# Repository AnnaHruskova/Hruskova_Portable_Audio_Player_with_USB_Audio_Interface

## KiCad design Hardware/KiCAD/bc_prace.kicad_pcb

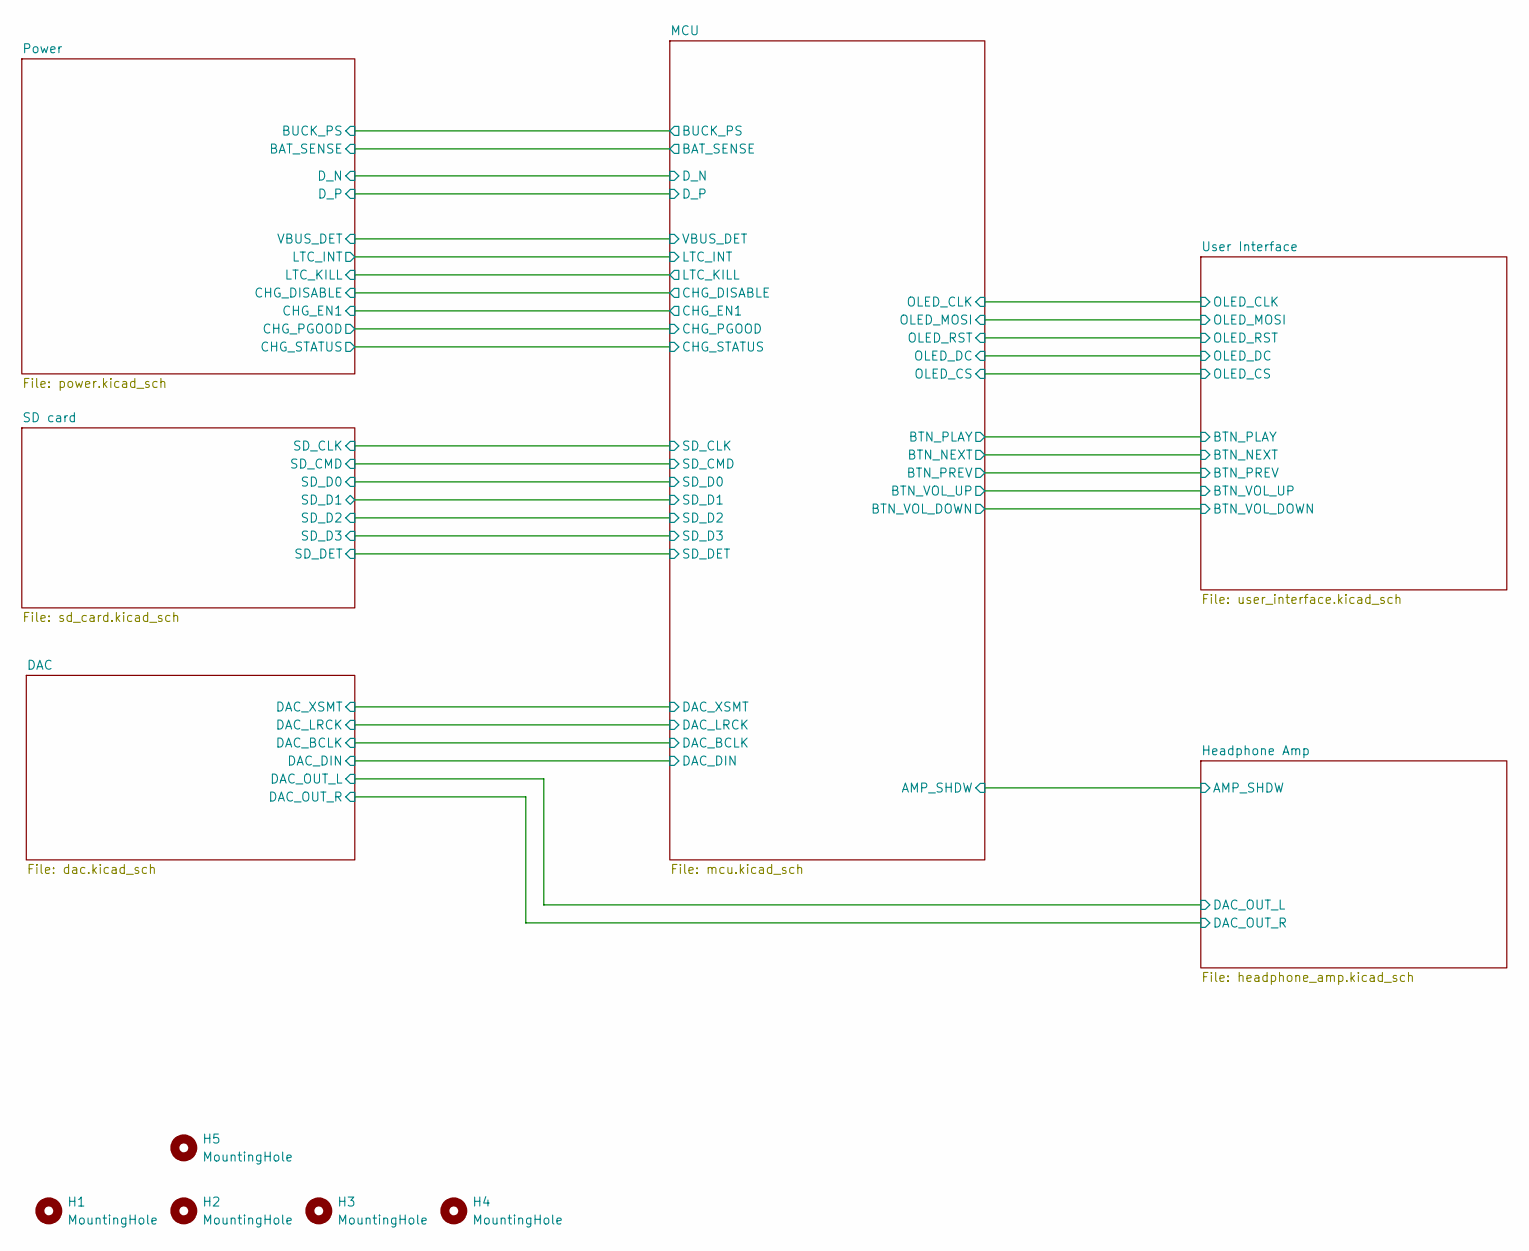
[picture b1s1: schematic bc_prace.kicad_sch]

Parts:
H1, H2, H3, H4: MountingHole; MountingHole_3.2mm_M3
H5: MountingHole; MountingHole_2.7mm

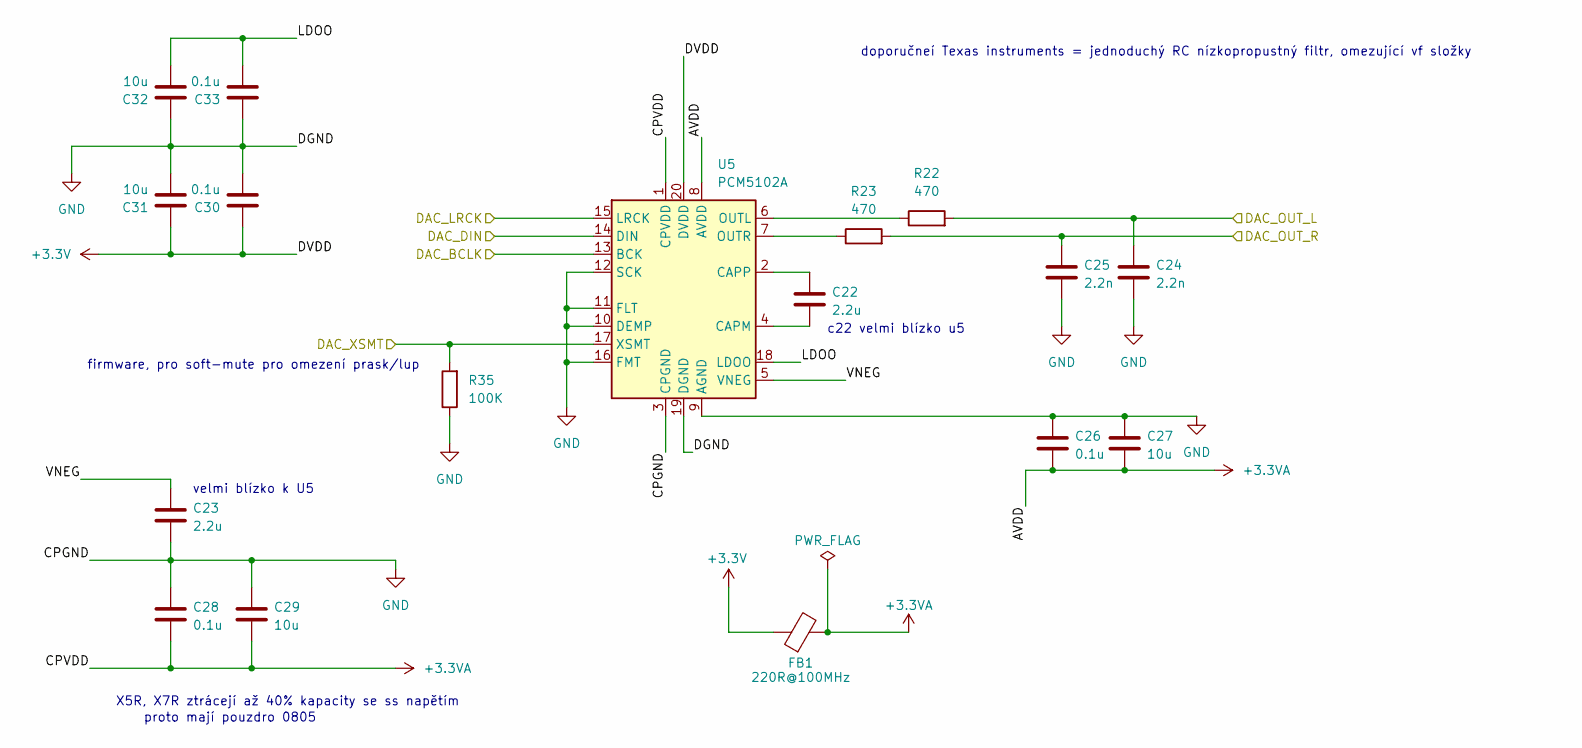
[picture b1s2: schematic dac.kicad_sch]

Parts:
C22, C23: 2.2u; C_0805_2012Metric; MPN CL21B225KOFNNNE
C24, C25: 2.2n; C_0603_1608Metric; MPN CC0603JRNPO9BN222
C26, C28, C33: 0.1u; C_0603_1608Metric; MPN CC0603KRX7R9BB104
C27, C29, C31: 10u; C_0805_2012Metric; MPN CL21A106KAYNNNE
C30: 0.1u; C_0805_2012Metric; MPN CC0805KRX7R9BB104
C32: 10u; C_0603_1608Metric; MPN CL10A106KP8NNNC
FB1: 220R@100MHz; L_0805_2012Metric; MPN BLM21PG221SN1D
R22, R23: 470; R_0603_1608Metric; MPN RC0603FR-07470RL
R35: 100K; R_0603_1608Metric; MPN RC0603FR-07100KL
U5: PCM5102A; TSSOP-20_4.4x6.5mm_P0.65mm; MPN PCM5102APWR

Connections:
+3.3V: C30.2, C31.2, FB1.1, U5.20 (DVDD); also elsewhere on the board
+3.3VA: C26.1, C27.1, C28.1, C29.1, FB1.2, U5.1 (CPVDD), U5.8 (AVDD)
/DAC/DAC_BCLK: U5.13 (BCK); also elsewhere on the board
/DAC/DAC_DIN: U5.14 (DIN); also elsewhere on the board
/DAC/DAC_LRCK: U5.15 (LRCK); also elsewhere on the board
/DAC/DAC_OUT_L: C24.2, R22.2; also elsewhere on the board
/DAC/DAC_OUT_R: C25.2, R23.2; also elsewhere on the board
/DAC/DAC_XSMT: R35.2, U5.17 (XSMT); also elsewhere on the board
/DAC/LDOO: C32.1, C33.1, U5.18 (LDOO)
/DAC/VNEG: C23.2, U5.5 (VNEG)
GND: C23.1, C24.1, C25.1, C26.2, C27.2, C28.2, C29.2, C30.1, C31.1, C32.2, C33.2, R35.1, U5.3 (CPGND), U5.9 (AGND), U5.10 (DEMP), U5.11 (FLT), U5.12 (SCK), U5.16 (FMT), U5.19 (DGND); also elsewhere on the board
unnamed: C22.1, U5.4 (CAPM)
unnamed: C22.2, U5.2 (CAPP)
unnamed: R22.1, U5.6 (OUTL)
unnamed: R23.1, U5.7 (OUTR)

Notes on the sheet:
proto mají pouzdro 0805
velmi blízko k U5
doporučneí Texas instruments = jednoduchý RC nízkopropustný filtr, omezující vf složky
c22 velmi blízko u5
X5R, X7R ztrácejí až 40% kapacity se ss napětím
firmware, pro soft-mute pro omezení prask/lup

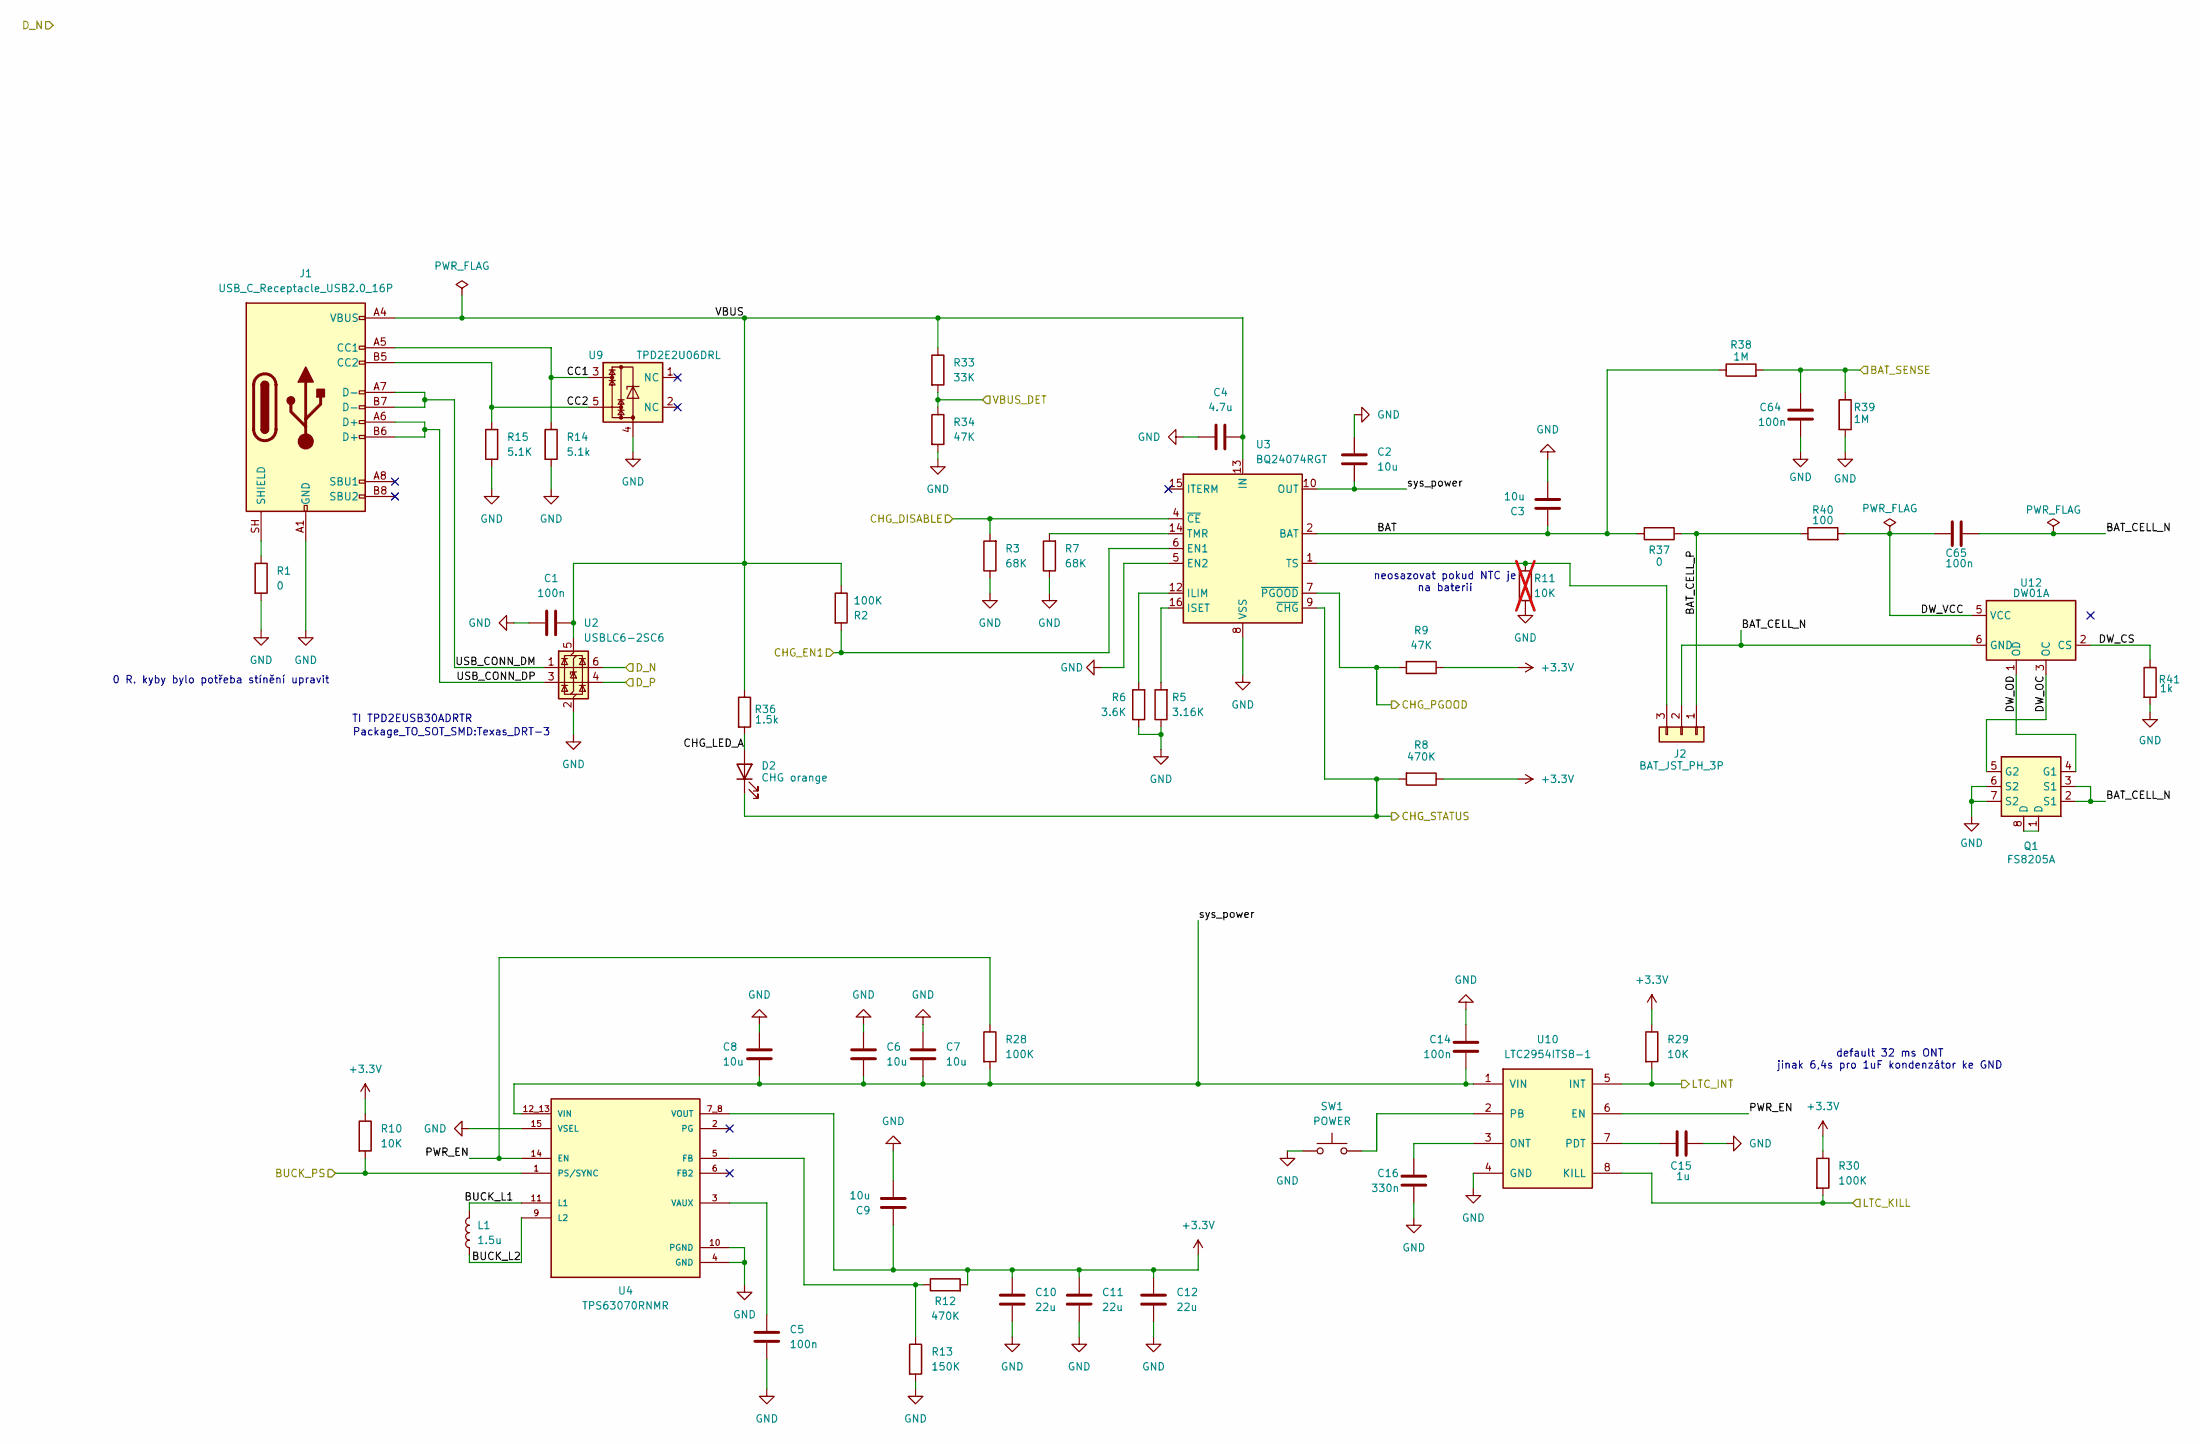
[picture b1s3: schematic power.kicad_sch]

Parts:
C1, C5, C14: 100n; C_0603_1608Metric; MPN CC0603KRX7R9BB104
C2: 10u; C_0805_2012Metric; MPN CL21B475KOFNNWE
C3, C6, C7, C8, C9: 10u; C_0805_2012Metric; MPN CL21A106KAYNNNE
C4: 4.7u; C_0603_1608Metric; MPN CL10A475KO8NNNC
C10, C11, C12: 22u; C_0805_2012Metric; MPN CL21A226MAQNNNE
C15: 1u; C_0603_1608Metric; MPN CL10A105KB8NNNC
C16: 330n; C_0603_1608Metric; MPN CC0603KRX7R7BB334
C64, C65: 100n; C_0805_2012Metric; MPN CC0805KRX7R9BB104
D2: CHG orange; LED_0805_2012Metric; MPN LED 0805 oranžová (doplnit)
J1: USB_C_Receptacle_USB2.0_16P; USB_C_Receptacle_GCT_USB4105-xx-A_16P_TopMnt_Horizontal; MPN USB4105-GF-A
J2: BAT_JST_PH_3P; JST_PH_B3B-PH-K_1x03_P2.00mm_Vertical; MPN B3B-PH-K-S(LF)(SN)
L1: 1.5u; L_Coilcraft_XxL4020; MPN XFL4020-152MEC
Q1: FS8205A; TSSOP-8_4.4x3mm_P0.65mm; MPN FS8205A
R1: 0; R_0603_1608Metric; MPN RC0603JR-070RL
R2, R28, R30: 100K; R_0603_1608Metric; MPN RC0603FR-07100KL
R3, R7: 68K; R_0603_1608Metric; MPN RC0603FR-0768KL
R5: 3.16K; R_0603_1608Metric
R6: 3.6K; R_0603_1608Metric; MPN RC0603FR-073K6L
R8, R12: 470K; R_0603_1608Metric; MPN RC0603FR-07470KL
R9, R34: 47K; R_0603_1608Metric; MPN RC0603FR-0747KL
R10, R29: 10K; R_0603_1608Metric; MPN RC0603FR-0710KL
R11: 10K; R_0603_1608Metric; MPN RC0603FR-0710KL; not fitted
R13: 150K; R_0603_1608Metric; MPN RC0603FR-07150KL
R14: 5.1k; R_0603_1608Metric; MPN RC0603FR-075K1L
R15: 5.1K; R_0603_1608Metric; MPN RC0603FR-075K1L
R33: 33K; R_0603_1608Metric; MPN RC0603FR-0733KL
R36: 1.5k; R_0805_2012Metric; MPN RC0805FR-071K5L
R37: 0; R_1206_3216Metric; MPN RC1206JR-070RL
R38, R39: 1M; R_0805_2012Metric; MPN RC0805FR-071ML
R40: 100; R_0805_2012Metric; MPN RC0805FR-07100RL
R41: 1k; R_0805_2012Metric; MPN RC0805FR-071KL
SW1: POWER; SW_Push_1P1T-MP_NO_Horizontal_Alps_SKRTLAE010; MPN SKRTLAE010
U2: USBLC6-2SC6; SOT-23-6; MPN USBLC6-2SC6
U3: BQ24074RGT; VQFN-16-1EP_3x3mm_P0.5mm_EP1.6x1.6mm
U4: TPS63070RNMR; VREG_TPS63070RNMR
U9: TPD2E2U06DRL; SOT-553; MPN TPD2E2U06DRLR
U10: LTC2954ITS8-1; TSOT-23-8; MPN LTC2954ITS8-1#TRMPBF
U12: DW01A; SOT-23-6; MPN DW01A

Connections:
+3.3V: C9.2, C10.2, C11.2, C12.2, R8.1, R9.1, R10.1, R12.2, R29.1, R30.1, U4.7_8 (VOUT); also elsewhere on the board
/MCU/BAT_SENSE: C64.1, R38.2, R39.1; also elsewhere on the board
/MCU/BUCK_PS: R10.2, U4.1 (PS/SYNC); also elsewhere on the board
/MCU/CHG_DISABLE: R3.2, U3.4 (~CE); also elsewhere on the board
/MCU/CHG_EN1: R2.2, U3.6 (EN1); also elsewhere on the board
/MCU/CHG_PGOOD: R9.2, U3.7 (~PGOOD); also elsewhere on the board
/MCU/CHG_STATUS: D2.1 (K), R8.2, U3.9 (~CHG); also elsewhere on the board
/MCU/D_N: U2.6 (I/O1); also elsewhere on the board
/MCU/D_P: U2.4 (I/O2); also elsewhere on the board
/MCU/LTC_INT: R29.2, U10.5 (INT); also elsewhere on the board
/MCU/LTC_KILL: R30.2, U10.8 (KILL); also elsewhere on the board
/MCU/VBUS_DET: R33.2, R34.1; also elsewhere on the board
/Power/BAT: C3.2, R37.2, R38.1, U3.2 (BAT), U3.3 (BAT)
/Power/BAT_CELL_N: C65.2, J2.2, Q1.2 (S1), Q1.3 (S1), U12.6 (GND)
/Power/BAT_CELL_P: J2.1, R37.1, R40.1
/Power/BUCK_L1: L1.2, U4.11 (L1)
/Power/BUCK_L2: L1.1, U4.9 (L2)
/Power/CC1: J1.A5 (CC1), R14.1, U9.3
/Power/CC2: J1.B5 (CC2), R15.2, U9.5
/Power/CHG_LED_A: D2.2 (A), R36.2
/Power/DW_CS: R41.1, U12.2 (CS)
/Power/DW_OC: Q1.5 (G2), U12.3 (OC)
/Power/DW_OD: Q1.4 (G1), U12.1 (OD)
/Power/DW_VCC: C65.1, R40.2, U12.5 (VCC)
/Power/PWR_EN: R28.1, U4.14 (EN), U10.6 (EN)
/Power/USB_CONN_DM: J1.A7 (D-), J1.B7 (D-), U2.1 (I/O1)
/Power/USB_CONN_DP: J1.A6 (D+), J1.B6 (D+), U2.3 (I/O2)
/Power/VBUS: C1.2, C4.2, J1.A4 (VBUS), J1.A9 (VBUS), J1.B4 (VBUS), J1.B9 (VBUS), R2.1, R33.1, R36.1, U2.5 (VBUS), U3.13 (IN)
/Power/sys_power: C2.2, C6.2, C7.2, C8.2, C14.2, R28.2, U3.10 (OUT), U3.11 (OUT), U4.12_13 (VIN), U10.1 (VIN)
GND: C1.1, C2.1, C3.1, C4.1, C5.2, C6.1, C7.1, C8.1, C9.1, C10.1, C11.1, C12.1, C14.1, C15.2, C16.2, C64.2, J1.A1 (GND), J1.A12 (GND), J1.B1 (GND), J1.B12 (GND), Q1.6 (S2), Q1.7 (S2), R1.2, R3.1, R5.1, R6.1, R7.1, R11.2, R13.2, R14.2, R15.1, R34.2, R39.2, R41.2, SW1.1, U2.2 (GND), U3.5 (EN2), U3.8 (VSS), U3.17 (VSS), U4.4 (GND), U4.10 (PGND), U4.15 (VSEL), U9.4, U10.4 (GND); also elsewhere on the board
unnamed: J1.SH (SHIELD), R1.1
unnamed: J2.3, R11.1, U3.1 (TS)
unnamed: Q1.1 (D), Q1.8 (D)
unnamed: R6.2, U3.12 (ILIM)
unnamed: R5.2, U3.16 (ISET)
unnamed: R7.2, U3.14 (TMR)
unnamed: R12.1, R13.1, U4.5 (FB)
unnamed: C5.1, U4.3 (VAUX)
unnamed: C16.1, U10.3 (ONT)
unnamed: SW1.2, U10.2 (PB)
unnamed: C15.1, U10.7 (PDT)

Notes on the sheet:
Package_TO_SOT_SMD:Texas_DRT-3
neosazovat pokud NTC je na baterii
default 32 ms ONT jinak 6,4s pro 1uF kondenzátor ke GND
0 R. kyby bylo potřeba stínění upravit
TI TPD2EUSB30ADRTR

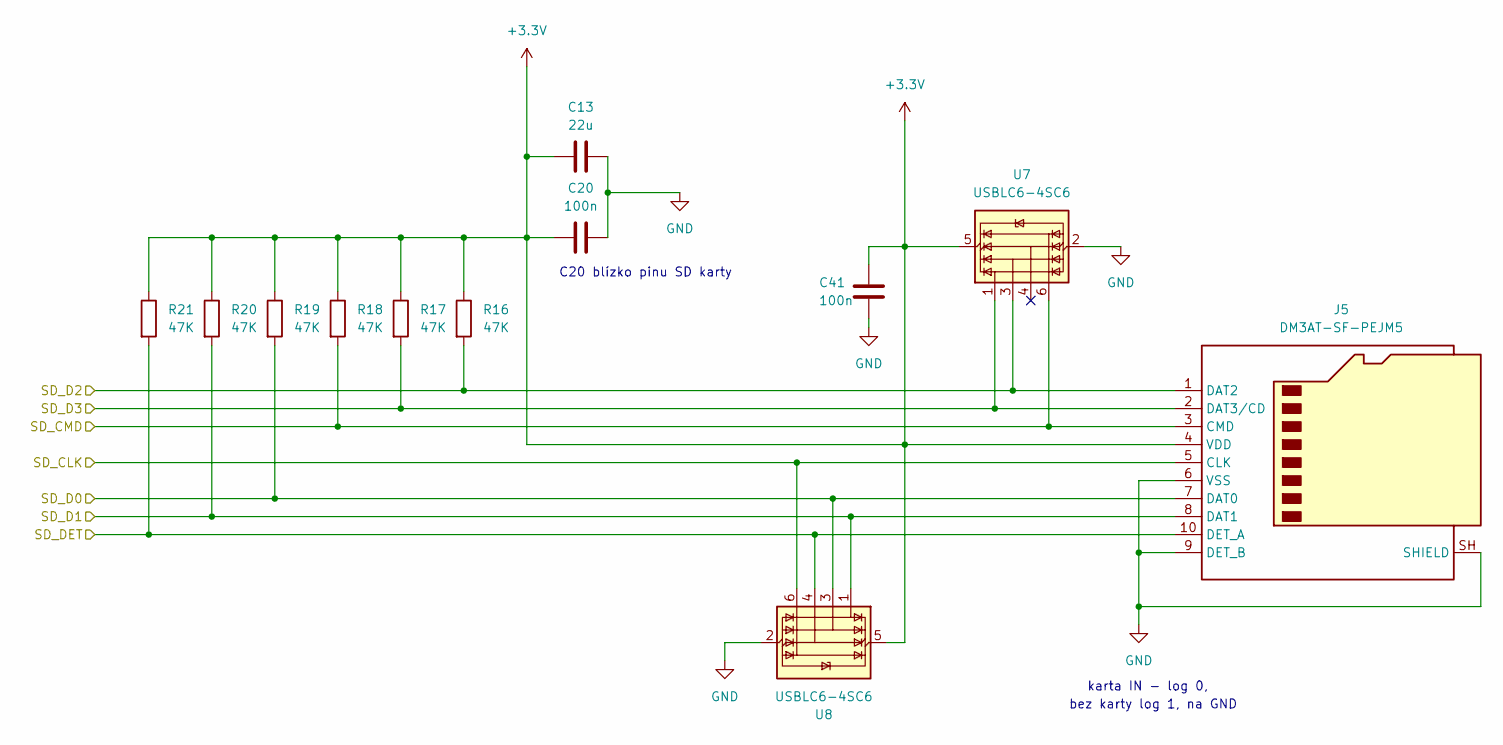
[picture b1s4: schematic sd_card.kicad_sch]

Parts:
C13: 22u; C_0805_2012Metric; MPN CL21A226MAQNNNE
C20, C41: 100n; C_0603_1608Metric; MPN CC0603KRX7R9BB104
J5: DM3AT-SF-PEJM5; microSD_HC_Hirose_DM3AT-SF-PEJM5; MPN DM3AT-SF-PEJM5
R16, R17, R18, R19, R20, R21: 47K; R_0603_1608Metric; MPN RC0603FR-0747KL
U7, U8: USBLC6-4SC6; SOT-23-6; MPN USBLC6-4SC6

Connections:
+3.3V: C13.2, C20.2, C41.1, J5.4 (VDD), R16.1, R17.1, R18.1, R19.1, R20.1, R21.1, U7.5 (VBUS), U8.5 (VBUS); also elsewhere on the board
/MCU/SD_CLK: J5.5 (CLK), U8.6 (I/O4); also elsewhere on the board
/MCU/SD_CMD: J5.3 (CMD), R18.2, U7.6 (I/O4); also elsewhere on the board
/MCU/SD_D0: J5.7 (DAT0), R19.2, U8.3 (I/O2); also elsewhere on the board
/MCU/SD_D1: J5.8 (DAT1), R20.2, U8.1 (I/O1); also elsewhere on the board
/MCU/SD_D2: J5.1 (DAT2), R16.2, U7.3 (I/O2); also elsewhere on the board
/MCU/SD_D3: J5.2 (DAT3/CD), R17.2, U7.1 (I/O1); also elsewhere on the board
/MCU/SD_DET: J5.10 (DET_A), R21.2, U8.4 (I/O3); also elsewhere on the board
GND: C13.1, C20.1, C41.2, J5.6 (VSS), J5.9 (DET_B), J5.SH (SHIELD), U7.2 (GND), U8.2 (GND); also elsewhere on the board

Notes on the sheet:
karta IN - log 0,
C20 blízko pinu SD karty
bez karty log 1, na GND

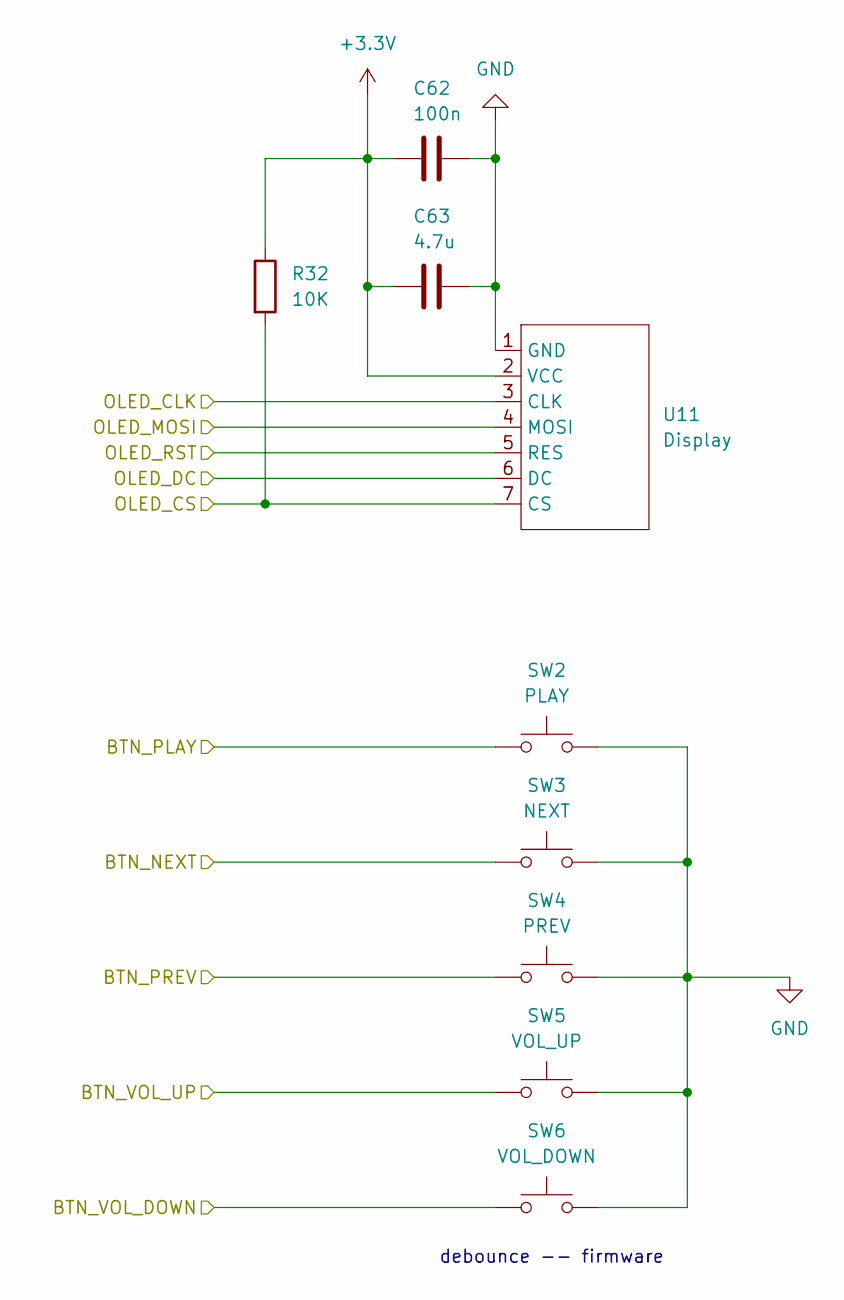
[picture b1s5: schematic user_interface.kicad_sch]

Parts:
C62: 100n; C_0603_1608Metric; MPN CC0603KRX7R9BB104
C63: 4.7u; C_0603_1608Metric; MPN CL10A475KO8NNNC
R32: 10K; R_0603_1608Metric; MPN RC0603FR-0710KL
SW2: PLAY; SW_SPST_PTS647_Sx70; MPN B3F-1000
SW3: NEXT; SW_SPST_PTS647_Sx70; MPN B3F-1000
SW4: PREV; SW_SPST_PTS647_Sx70; MPN B3F-1000
SW5: VOL_UP; SW_Push_1P1T-MP_NO_Horizontal_Alps_SKRTLAE010; MPN SKRTLAE010
SW6: VOL_DOWN; SW_Push_1P1T-MP_NO_Horizontal_Alps_SKRTLAE010; MPN SKRTLAE010
U11: Display; OLED_SPI_7pin_P2.54mm; MPN OLED modul SPI 7pin (zakoupený vlastní)

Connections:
+3.3V: C62.1, C63.1, R32.1, U11.2 (VCC); also elsewhere on the board
/MCU/BTN_NEXT: SW3.1; also elsewhere on the board
/MCU/BTN_PLAY: SW2.1; also elsewhere on the board
/MCU/BTN_PREV: SW4.1; also elsewhere on the board
/MCU/BTN_VOL_DOWN: SW6.1; also elsewhere on the board
/MCU/BTN_VOL_UP: SW5.1; also elsewhere on the board
/MCU/OLED_CLK: U11.3 (CLK); also elsewhere on the board
/MCU/OLED_CS: R32.2, U11.7 (CS); also elsewhere on the board
/MCU/OLED_DC: U11.6 (DC); also elsewhere on the board
/MCU/OLED_MOSI: U11.4 (MOSI); also elsewhere on the board
/MCU/OLED_RST: U11.5 (RES); also elsewhere on the board
GND: C62.2, C63.2, SW2.2, SW3.2, SW4.2, SW5.2, SW6.2, U11.1 (GND); also elsewhere on the board

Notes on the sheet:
debounce -- firmware

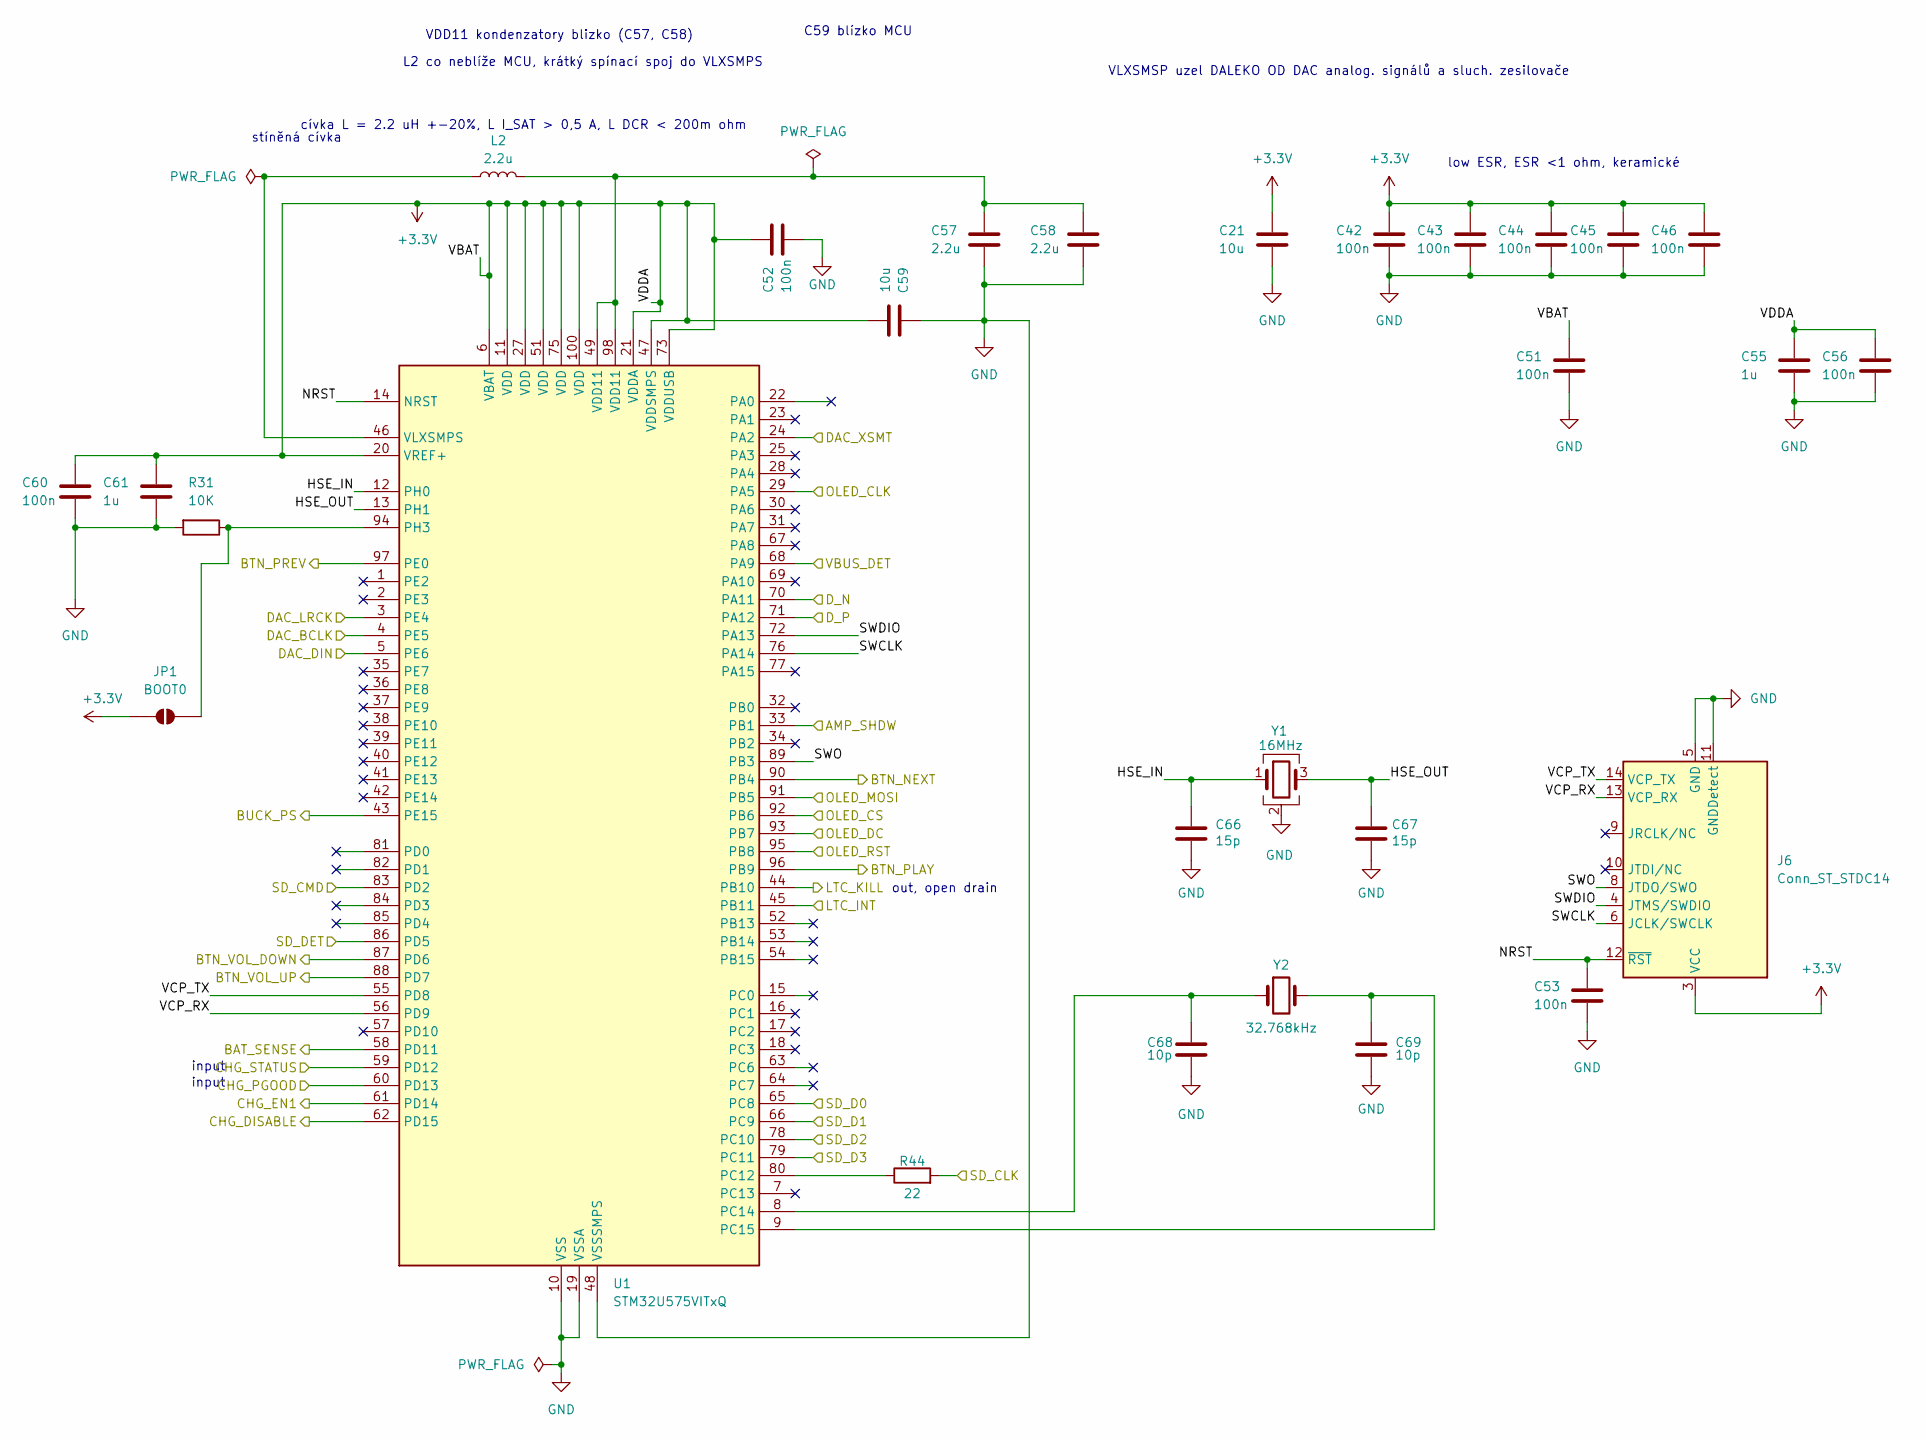
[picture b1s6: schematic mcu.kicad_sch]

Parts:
C21: 10u; C_0805_2012Metric; MPN CL21A106KAYNNNE
C42, C43, C44, C45, C46, C51, C52, C53, C56, C60: 100n; C_0603_1608Metric; MPN CC0603KRX7R9BB104
C55, C61: 1u; C_0603_1608Metric; MPN CL10A105KB8NNNC
C57, C58: 2.2u; C_0603_1608Metric; MPN CL10A225KO8NNNC
C59: 10u; C_1206_3216Metric; MPN C3216X7R1C106K160AC
C66, C67: 15p; C_0805_2012Metric; MPN CC0805JRNPO9BN150
C68, C69: 10p; C_0805_2012Metric; MPN CC0805JRNPO9BN100
J6: Conn_ST_STDC14; PinHeader_2x07_P1.27mm_Vertical_SMD
JP1: BOOT0; SolderJumper-2_P1.3mm_Open_RoundedPad1.0x1.5mm
L2: 2.2u; L_Coilcraft_XxL4020; MPN XFL4020-222MEC
R31: 10K; R_0603_1608Metric; MPN RC0603FR-0710KL
R44: 22; R_0805_2012Metric; MPN RC0805FR-0722RL
U1: STM32U575VITxQ; LQFP-100_14x14mm_P0.5mm
Y1: 16MHz; Crystal_SMD_3225-4Pin_3.2x2.5mm; MPN 16 MHz, 3225, CL 10 pF, +-20 ppm (dopln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
Y2: 32.768kHz; Crystal_SMD_3215-2Pin_3.2x1.5mm; MPN FC-135R 32.768KA-AC

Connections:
+3.3V: C21.2, C42.2, C43.2, C44.2, C45.2, C46.2, C51.2, C52.2, C55.2, C56.2, C59.1, C60.2, C61.2, J6.3 (VCC), JP1.1 (A), U1.6 (VBAT), U1.11 (VDD), U1.20 (VREF+), U1.21 (VDDA), U1.27 (VDD), U1.47 (VDDSMPS), U1.51 (VDD), U1.73 (VDDUSB), U1.75 (VDD), U1.100 (VDD); also elsewhere on the board
/DAC/DAC_BCLK: U1.4 (PE5); also elsewhere on the board
/DAC/DAC_DIN: U1.5 (PE6); also elsewhere on the board
/DAC/DAC_LRCK: U1.3 (PE4); also elsewhere on the board
/DAC/DAC_XSMT: U1.24 (PA2); also elsewhere on the board
/Headphone Amp/AMP_SHDW: U1.33 (PB1); also elsewhere on the board
/MCU/BAT_SENSE: U1.58 (PD11); also elsewhere on the board
/MCU/BTN_NEXT: U1.90 (PB4); also elsewhere on the board
/MCU/BTN_PLAY: U1.96 (PB9); also elsewhere on the board
/MCU/BTN_PREV: U1.97 (PE0); also elsewhere on the board
/MCU/BTN_VOL_DOWN: U1.87 (PD6); also elsewhere on the board
/MCU/BTN_VOL_UP: U1.88 (PD7); also elsewhere on the board
/MCU/BUCK_PS: U1.43 (PE15); also elsewhere on the board
/MCU/CHG_DISABLE: U1.62 (PD15); also elsewhere on the board
/MCU/CHG_EN1: U1.61 (PD14); also elsewhere on the board
/MCU/CHG_PGOOD: U1.60 (PD13); also elsewhere on the board
/MCU/CHG_STATUS: U1.59 (PD12); also elsewhere on the board
/MCU/D_N: U1.70 (PA11); also elsewhere on the board
/MCU/D_P: U1.71 (PA12); also elsewhere on the board
/MCU/HSE_IN: C66.1, U1.12 (PH0), Y1.1
/MCU/HSE_OUT: C67.1, U1.13 (PH1), Y1.3
/MCU/LTC_INT: U1.45 (PB11); also elsewhere on the board
/MCU/LTC_KILL: U1.44 (PB10); also elsewhere on the board
/MCU/NRST: C53.2, J6.12 (~RST), U1.14 (NRST)
/MCU/OLED_CLK: U1.29 (PA5); also elsewhere on the board
/MCU/OLED_CS: U1.92 (PB6); also elsewhere on the board
/MCU/OLED_DC: U1.93 (PB7); also elsewhere on the board
/MCU/OLED_MOSI: U1.91 (PB5); also elsewhere on the board
/MCU/OLED_RST: U1.95 (PB8); also elsewhere on the board
/MCU/SD_CLK: R44.2; also elsewhere on the board
/MCU/SD_CMD: U1.83 (PD2); also elsewhere on the board
/MCU/SD_D0: U1.65 (PC8); also elsewhere on the board
/MCU/SD_D1: U1.66 (PC9); also elsewhere on the board
/MCU/SD_D2: U1.78 (PC10); also elsewhere on the board
/MCU/SD_D3: U1.79 (PC11); also elsewhere on the board
/MCU/SD_DET: U1.86 (PD5); also elsewhere on the board
/MCU/SWCLK: J6.6 (JCLK/SWCLK), U1.76 (PA14)
/MCU/SWDIO: J6.4 (JTMS/SWDIO), U1.72 (PA13)
/MCU/SWO: J6.8 (JTDO/SWO), U1.89 (PB3)
/MCU/VBUS_DET: U1.68 (PA9); also elsewhere on the board
/MCU/VCP_RX: J6.13 (VCP_RX), U1.56 (PD9)
/MCU/VCP_TX: J6.14 (VCP_TX), U1.55 (PD8)
GND: C21.1, C42.1, C43.1, C44.1, C45.1, C46.1, C51.1, C52.1, C53.1, C55.1, C56.1, C57.1, C58.1, C59.2, C60.1, C61.1, C66.2, C67.2, C68.2, C69.2, J6.5 (GND), J6.7 (GND), J6.11 (GNDDetect), R31.2, U1.10 (VSS), U1.19 (VSSA), U1.26 (VSS), U1.48 (VSSSMPS), U1.50 (VSS), U1.74 (VSS), U1.99 (VSS), Y1.2 (G), Y1.4 (G); also elsewhere on the board
unnamed: C57.2, C58.2, L2.2, U1.49 (VDD11), U1.98 (VDD11)
unnamed: JP1.2 (B), R31.1, U1.94 (PH3)
unnamed: R44.1, U1.80 (PC12)
unnamed: C68.1, U1.8 (PC14), Y2.1
unnamed: C69.1, U1.9 (PC15), Y2.2
unnamed: L2.1, U1.46 (VLXSMPS)

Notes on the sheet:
VLXSMSP uzel DALEKO OD DAC analog. signálů a sluch. zesilovače
input
L2 co neblíže MCU, krátký spínací spoj do VLXSMPS
stíněná cívka
C59 blízko MCU
low ESR, ESR <1 ohm, keramické
out, open drain
VDD11 kondenzatory blizko (C57, C58)
cívka L = 2.2 uH +-20%, L I_SAT > 0,5 A, L DCR < 200m ohm

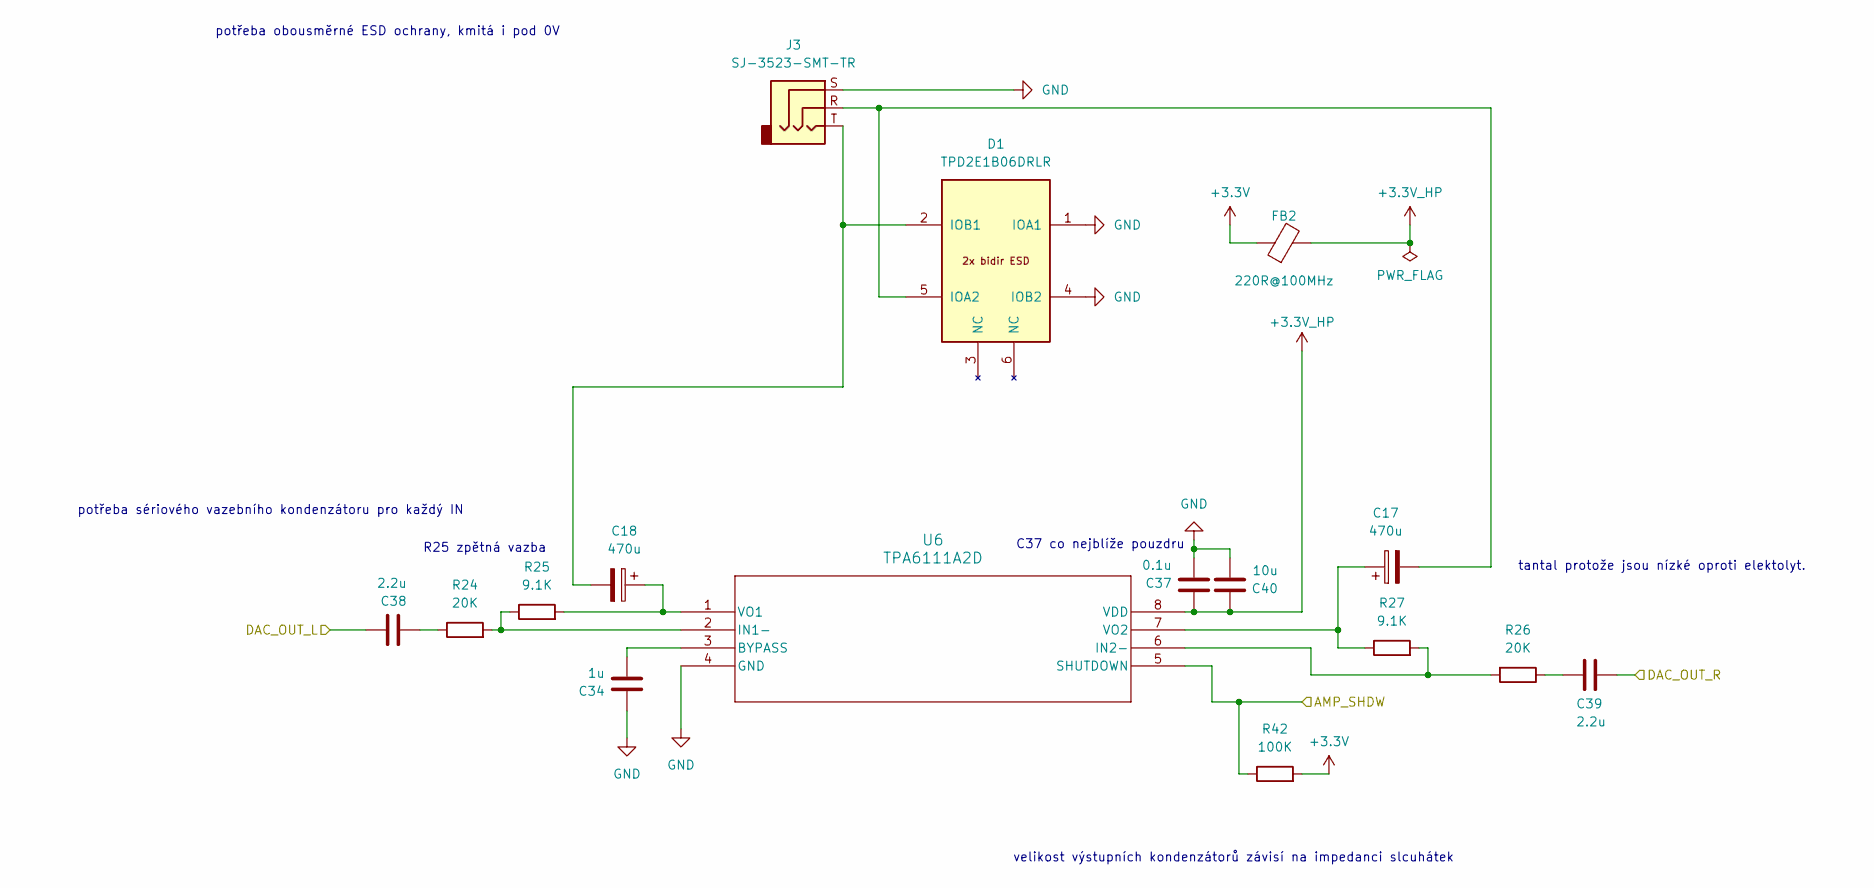
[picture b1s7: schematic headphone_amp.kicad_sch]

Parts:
C17, C18: 470u; CP_EIA-7343-31_Kemet-D; MPN T520D477M006ATE015; LCSC C696809
C34: 1u; C_0603_1608Metric; MPN CL10A105KB8NNNC
C37: 0.1u; C_0603_1608Metric; MPN CC0603KRX7R9BB104
C38: 2.2u; C_0805_2012Metric; MPN GRM21BR71C225KA12L
C39: 2.2u; C_0805_2012Metric
C40: 10u; C_0805_2012Metric; MPN CL21A106KAYNNNE
D1: TPD2E1B06DRLR; SOT-563
FB2: 220R@100MHz; L_0805_2012Metric; MPN BLM21PG221SN1D
J3: SJ-3523-SMT-TR; Jack_3.5mm_CUI_SJ1-3523N_Horizontal; MPN SJ1-3523N; LCSC C20182914
R24, R26: 20K; R_0603_1608Metric; MPN RT0603BRD0720KL
R25, R27: 9.1K; R_0603_1608Metric; MPN RT0603BRD079K1L
R42: 100K; R_0603_1608Metric; MPN RC0603FR-07100KL
U6: TPA6111A2D; SOIC-8_3.9x4.9mm_P1.27mm

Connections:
+3.3V: FB2.1, R42.2; also elsewhere on the board
+3.3V_HP: C37.2, C40.2, FB2.2, U6.8 (VDD)
/DAC/DAC_OUT_L: C38.2; also elsewhere on the board
/DAC/DAC_OUT_R: C39.2; also elsewhere on the board
/Headphone Amp/AMP_SHDW: R42.1, U6.5 (SHUTDOWN); also elsewhere on the board
GND: C34.2, C37.1, C40.1, D1.1 (IOA1), D1.4 (IOB2), J3.S, U6.4 (GND); also elsewhere on the board
unnamed: C38.1, R24.1
unnamed: C39.1, R26.1
unnamed: C17.2, D1.5 (IOA2), J3.R
unnamed: C18.2, D1.2 (IOB1), J3.T
unnamed: C34.1, U6.3 (BYPASS)
unnamed: R24.2, R25.1, U6.2 (IN1-)
unnamed: R26.2, R27.2, U6.6 (IN2-)
unnamed: C18.1, R25.2, U6.1 (VO1)
unnamed: C17.1, R27.1, U6.7 (VO2)

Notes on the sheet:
potřeba obousměrné ESD ochrany, kmitá i pod 0V
tantal protože jsou nízké oproti elektolyt.
velikost výstupních kondenzátorů závisí na impedanci slcuhátek
potřeba sériového vazebního kondenzátoru pro každý IN
R25 zpětná vazba
C37 co nejblíže pouzdru

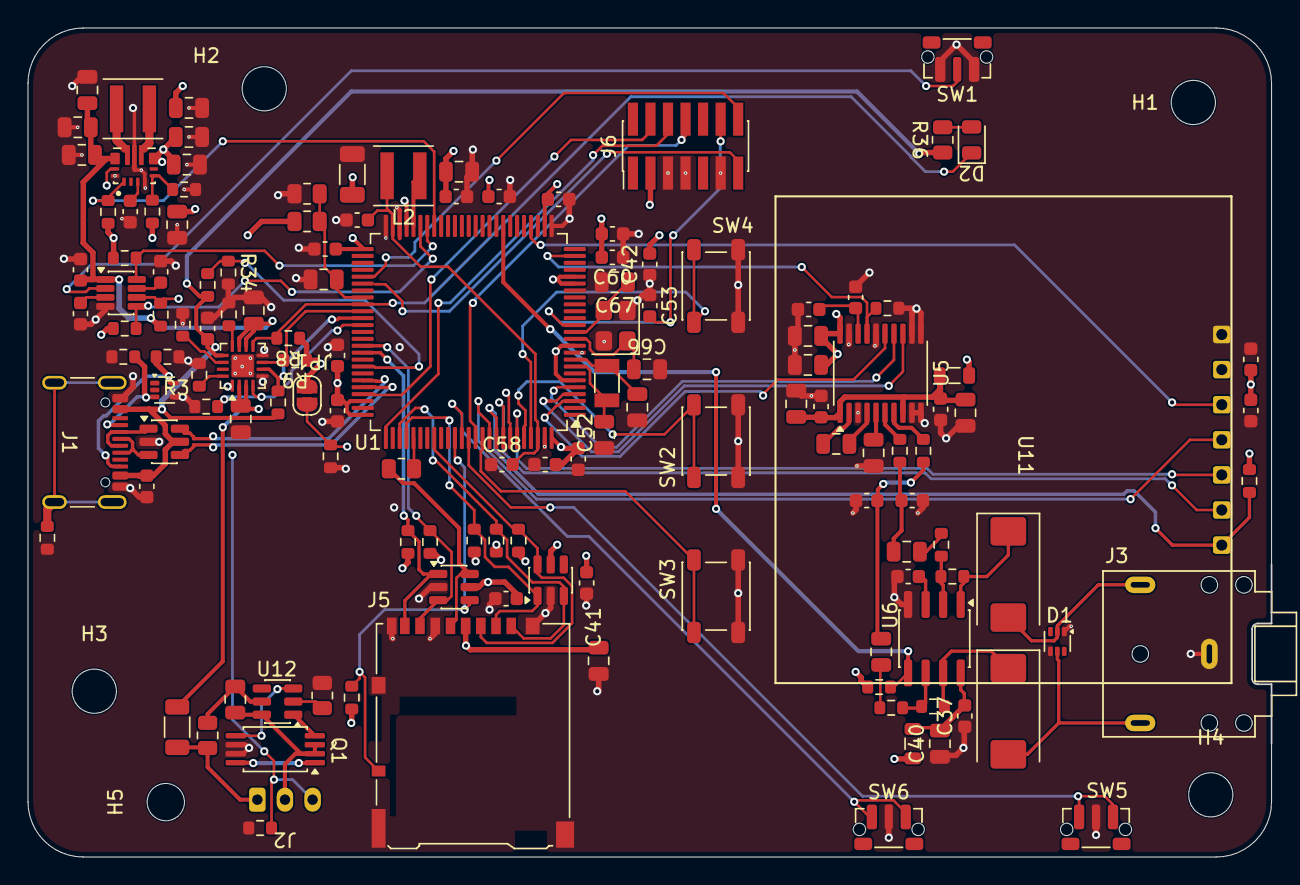
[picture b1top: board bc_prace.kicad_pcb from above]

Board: 4 copper layers, 90.0 x 60.0 mm, 141 parts (1 on the bottom side), 96 nets.
